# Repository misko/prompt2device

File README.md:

# prompt2device

The separate [vNext PCB skill and orchestrator](vnext/README.md) package is
available alongside the reference workflow below; existing projects keep their
accepted toolchain until an explicit migration.

The [Crow carrier + pod public design package](projects/crow-array/README.md)
provides native designs and fabrication exports for the 5-carrier/10-pod prototype
batch. It is a subset of the local sealed release, **not order authorization**.

**Prompt to device:** give an agent a plain-language hardware brief, work
through explicit design, review, and physical-test cycles, and finish with the
artifacts needed to manufacture the device—not merely a plausible CAD image.

## Quick start

### 1. Give the PCB skill a brief

```text
/pcb-design 3S LiPo input → 4× USB-A outputs at 5 V / 1.5 A each + 1× USB-C output at 5 V / 5 A.
```

### 2. See fabricated examples

These two projects show the path from a plain-English request to electrical
CAD, mechanical CAD, and fabricated hardware. The prompt cells preserve the
compact original wording; the links retain the corresponding design-lineage
records. Photographs are bench evidence, not production-qualification claims.
Exact provenance and claim limits are in
[`fabricated-examples.md`](docs/fabricated-examples.md).

|  | **Pluto eight-way fast switch** | **3S LiPo USB power board** |
|---|---|---|
| **Prompt** | [“we want a high speed 8 antenna switching board that can be programmed by the rpi4 and run with a pluto+”](archived_projects/pluto-rx2-8way/01_docs/BRIEF.md#original-prompt) | [“Please from scratch start a new project, and lets design a board that takes 3S lipo XT60 power as input , and outputs 3 x USB A ports (2.5A max) and 1 x USB C port (6A max).”](archived_projects/usb-power-3s/01_docs/BRIEF.md#original-prompt) |
| **PCB rendering** |  |  |
| **Enclosure rendering** |  |  |
| **Fabricated board** |  |  |
| **Board in enclosure** |  |  |
| **Bench setup** |  |  |

[`pluto-rx2-8way-v5`](projects/pluto-rx2-8way-v5/) is the fabricated
eight-way RF switch board. Its immutable PCB design archive is
[`v0.2.1-2026-08-14`](projects/pluto-rx2-8way-v5/07_releases/v0.2.1-2026-08-14/),
with a sealed
[3D PCB render](projects/pluto-rx2-8way-v5/07_releases/v0.2.1-2026-08-14/verification/final_iso_3200.png),
and its independently versioned
[`v0.8.0-2026-08-28` enclosure](projects/pluto-rx2-8way-v5/07_enclosure_releases/v0.8.0-2026-08-28/)
has a corresponding
[installed-assembly render](projects/pluto-rx2-8way-v5/07_enclosure_releases/v0.8.0-2026-08-28/renders/installed-assembly.png).
That enclosure remains an honest `INCOMPLETE` candidate pending sliced and
printed fit, retention, connector-service, and thermal tests.
The PCB archive itself predates fabrication and still records
`DO-NOT-ORDER`; RF first-article measurements remain open.
The current human-readable engineering study is
[RF isolation, leakage paths, and a v6 mitigation strategy](projects/pluto-rx2-8way-v5/01_docs/reports/2026-08-27-rf-isolation-and-v6-mitigation.md).

[`usb-hub-3s-v3`](projects/usb-hub-3s-v3/) is the closest existing hardware
to the quick-start brief: three USB-A outputs and one USB-C output rather than
four USB-A outputs. Its latest sealed and fabricated archive is
[`v1.12-2026-07-28`](projects/usb-hub-3s-v3/07_releases/v1.12-2026-07-28/).
The [bring-up journal](projects/usb-hub-3s-v3/01_docs/journal/bringup.md)
records physical v1.12 boards and the replacement assembly's successful
no-load regulation checks; full load, transient, and thermal qualification is
still open.

The exact v1.12 board also has an independently versioned
[`v0.4.0-2026-08-28` enclosure](projects/usb-hub-3s-v3/07_enclosure_releases/v0.4.0-2026-08-28/)
with a corresponding
[installed-assembly render](projects/usb-hub-3s-v3/07_enclosure_releases/v0.4.0-2026-08-28/renders/installed-assembly.png).
Its [authored source and replay instructions](projects/usb-hub-3s-v3/03_src/mechanical/README.md)
remain mutable, while the release is an immutable `INCOMPLETE` candidate:
structural and collision screens pass, but printed fit, connector service,
retention, and thermal evidence remain open.

### 3. Follow the prompt-to-device loop

```text
plain-language brief
  → fact locks and architecture
  → schematic, placement, routing, and enclosure development
  ↺ independent review, correction, regeneration, and measurement
  → sealed fabrication and mechanical artifacts
  → first article, physical findings, and the next development cycle
```

Today the governed output can include:

- native KiCad schematics and a rendered schematic PDF;
- the routed KiCad PCB plus Gerbers, drill files, BOM, and CPL for fabrication;
- top, bottom, and 3D PCB renders plus a STEP assembly;
- when mechanical work is selected, enclosure source, printable STLs, assembly
  renders, and clearance evidence; and
- governed Markdown investigations under each project's `01_docs/reports/`.

The pipeline already uses board-level CAD/assembly twins as verification
instruments. Governed firmware releases and an integrated product-level digital
twin are forward work, tracked by
[IMP-234](improvements.md#imp-234--firmware-release-stream) and
[IMP-236](improvements.md#imp-236--prompt-to-device-product-composition-and-digital-twin).

## What this repository is

`prompt2device` is a code-first prompt-to-device engineering system. It turns a
user brief into generated KiCad source, bounded routing candidates,
independently graded fabrication evidence, immutable releases, printable
enclosures, and measured first-article records.

The product is the workflow under [`skills/`](skills/). Boards under
[`projects/`](projects/) are its active applications; sealed release folders
are immutable evidence, not templates to copy.

## Manual commissioning

Clone the repository, create a branch, and save the user's original request as
a UTF-8 text file:

```bash
git clone https://github.com/misko/prompt2device.git
cd prompt2device
git switch -c codex/my-board
```

Create the governed project scaffold and choose its capability profile:

```bash
python3 skills/pcb-design/scripts/commission_project.py my-board \
  --brief-file /path/to/original-brief.txt \
  --signal-integrity ordinary \
  --assembly jlcpcb \
  --firmware forbidden \
  --target design
```

Use `high_speed_digital` for USB and similar controlled digital links. Use
`rf` only when the board intentionally carries RF/microwave signals. Add
`--foreign-mating` when the floorplan consumes geometry from third-party
hardware. Run the command with `--help` for enclosure and target options.
Here `--assembly jlcpcb` selects the populated JLCPCB PCBA evidence path, not
merely bare-board fabrication.

The command reports `PCB-SCAFFOLD OK` and leaves `PCB-COMMISSION` explicitly
`INCOMPLETE`. It preserves the prompt and creates an executable commission
hold; it does not accept requirements, adopt the seeded schema examples, or
run a board producer.

Inspect the selected lifecycle before spending engineering time:

```bash
python3 skills/pcb-design/scripts/skill_reference_router.py \
  --profile projects/my-board/01_docs/capability-profile.json \
  --at-stage PCB-COMMISSION \
  --json
```

Then give Codex this instruction:

```text
Read and follow skills/pcb-design/SKILL.md for projects/my-board. Preserve the
original brief, close the commission fact locks, and stop at the first evidence
or operator checkpoint. Do not create firmware unless the brief explicitly
asks.
```

Do not run `rebuild_all.sh` yet. The scaffold contains visible schema examples
and `01_docs/COMMISSIONING-HOLD.md`; both rebuild conductors refuse to run until
the commission boundary is reviewed and that marker is deliberately removed.

Start with [`skills/pcb-design/SKILL.md`](skills/pcb-design/SKILL.md). Its
canonical lifecycle and runnable command map is
[`execution-graph.md`](skills/pcb-design/references/execution-graph.md).

## How execution is structured

The repository deliberately separates three layers:

```text
capability profile
  -> disclosure graph (what stages/references are selected)
  -> project conductor (what bounded commands actually run)
  -> owning gates (what exact subjects passed)
  -> review/seal/publication/physical claims
```

- The router is planning only. Its output is never execution evidence.
- `projects/<name>/03_src/rebuild_all.sh` is the full source/schematic
  conductor. It intentionally pauses at review and operator checkpoints.
- `rebuild_reuse.sh` is the deterministic route-authority replay when the
  schematic is unchanged; `route.yaml` selects the authenticated source.
- Fresh route exploration is a separate candidate workflow; canonical rebuild
  replays the authenticated route source selected by `route.yaml`.
- Layout seal, PCB release seal, publication, ordering, and first article are
  different claims with different owners.

The declarative lifecycle is:

```text
commission -> architecture -> sourcing
  -> schematic -> placement -> routing -> layout seal
  -> fabrication -> assembly verification
  -> release review -> release seal
  -> publication | first article -> production
```

RF context/source/realized/fabrication stages and foreign-mating import are
conditional branches. High-speed digital composes inside the ordinary stages.
Enclosures have an implemented parallel **INCOMPLETE-candidate** release stream
and may bind an unchanged PCB release without resealing it. Higher readiness
still requires the enclosure skill's recomputable CAD and physical evidence.
Firmware is currently an explicit handoff,
not a governed release stream; [IMP-234](improvements.md#imp-234--firmware-release-stream)
tracks that missing boundary.

## Skills and authority

| Skill | Owns |
|---|---|
| [`pcb-design`](skills/pcb-design/SKILL.md) | Commission, lifecycle composition, backtracking, reviews, release seal, publication, first article. |
| [`kicad-pcb`](skills/kicad-pcb/SKILL.md) | TSX/KiCad schematic conversion, netlist/parity, placement, geometry, routing, DRC, SI/RF realization. |
| [`jlcpcb-fab`](skills/jlcpcb-fab/SKILL.md) | Gerber/drill/BOM/CPL, stock/population/rotation, JLC CAD twin, manufacturer staging, bring-up cards. |
| [`pcb-enclosure`](skills/pcb-enclosure/SKILL.md) | Mechanical commission, PCB interface binding, independent fasteners, motion/clearance, mesh/physical evidence, enclosure releases. |
| [`shopping-list`](skills/shopping-list/SKILL.md) | Provenance-bound purchase lists for self-supplied parts. |

Authority is singular. A skill links to another owner's procedure rather than
copying it. Project `contracts.md` files own exact artifact membership. Script
`--help` text owns exact flags. [`improvements.md`](improvements.md) tracks
work and rationale but never overrides an executable gate or accepted ADR.

## Repository map

| Path | Purpose |
|---|---|
| [`skills/`](skills/) | Reusable workflow, references, tools, and project templates. |
| [`projects/`](projects/) | Active boards, including manufactured and still-evolving designs. |
| [`archived_projects/`](archived_projects/) | Retired scaffolds and frozen regression/history units. |
| [`docs/`](docs/) | Documentation index, accepted ADRs, measured proof, and historical context. |
| [`tests/`](tests/) | Clean and known-bad fixtures proving gates can both pass and fail. |
| [`external_hardware/`](external_hardware/) | Measured/cited facts about foreign devices this repo must mate with. |
| [`improvements.md`](improvements.md) | Forward work registry and retained improvement history. |

See [`docs/README.md`](docs/README.md) for the documentation authority map.

## Design model

The board is generated from committed human-owned source:

- TSX/tscircuit is the standard schematic authoring front end.
- Shared scripts convert the circuit, generate KiCad geometry/rules, and grade
  exact identities. Per-board source is configuration, not a copied backend.
- KiCad's Python API owns geometry and saves; `kicad-cli` owns headless
  ERC/DRC/netlist/export checks.
- Routing operates on immutable candidates. Only a clean, independently graded
  candidate can become the promoted route chain.
- Generated `04_kicad/` is a mutable current snapshot and is never hand-source
  authority. Immutable history lives under release streams.

This makes design changes diffable and rebuildable. It also means a generator
defect can become a physical defect, so freshness, parity, nonzero coverage,
registered models, and independent review are first-class gates.

## Claims and releases

A release is an immutable reviewed candidate archive. It is not automatically
an order event. A design can be electrically sound and sealed while remaining
`DO-NOT-ORDER` because stock, uploader selections, physical fit, or first-
article evidence is owed.

PCB and enclosure versions are independent streams. Current enclosure release
tooling publishes immutable `INCOMPLETE` candidates bound to one exact PCB
release without forcing that PCB to be resealed; it does not yet publish a
higher readiness claim from caller-supplied scope status.
A future firmware stream, exact product lock, and integrated product-level
digital twin remain tracked work, not current release authority.

## Toolchain

Core documentation and planning use normal Python 3. KiCad operations require
the KiCad-bundled Python where `import pcbnew` succeeds plus `kicad-cli`.
TSX generation requires the pinned tscircuit/Bun environment. Fresh routing
requires the configured KiCadRoutingTools installation; replaying a selected
authenticated route authority does not.

Python entry points expose `--help`; shell-conductor forms are documented in
the execution graph. Use the owning current command rather than copying an old
invocation from a project journal.

## Validate a workflow change

At minimum:

```bash
python3 skills/pcb-design/scripts/skill_authority_check.py
python3 tests/t1_skill_progressive_disclosure.py
python3 tests/t1_pcb_documentation.py
python3 scripts/contracts_audit.py --walk --root skills/pcb-design
```

Run the domain suites affected by the change, then commit at a green boundary.

## License

Except where otherwise noted, all original content in this repository is
licensed under the [MIT License](LICENSE). This includes software,
documentation, prompts, schematics, PCB layouts, mechanical CAD files,
and generated design artifacts.

Third-party materials remain subject to their respective copyright and
license terms and are not relicensed by this repository.

See [third-party notices](THIRD_PARTY_NOTICES.md) for material provenance and
[contribution guidelines](CONTRIBUTING.md) for new submissions.

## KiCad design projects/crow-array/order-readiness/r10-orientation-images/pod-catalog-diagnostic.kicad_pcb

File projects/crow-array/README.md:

# Crow carrier and microphone pod

[Open the public v3 design package](releases/crow-prototype-v3-first-run-5c10p-public-v1/README.md).
It contains **5 carrier / 10 pod** design quantities, native KiCad files, PDFs,
Gerbers, BOM/CPL, population policy and retained verification records.

This is a redistribution-reviewed subset, not the full original sealed offline
replay. The original design verdict is SOUND; the ordering verdict remains
**DO-NOT-ORDER**. No firmware or manufactured-hardware qualification is supplied.
The package index exposes all nine exact-job holds and its excluded dependencies.

For the current assembly split, sourcing worksheets and browser-based ordering
continuation, start with the [MacBook handoff](order-readiness/MACBOOK-HANDOFF.md).
These mutable preparation records do not change the immutable release verdict.

`publication.py verify` checks the actual file census, trusted source hashes,
both board roles, local native libraries, license/handoff policy and Gerber ZIPs.
`test_publication.py` corrupts isolated copies to prove that the checker refuses
missing boards, altered/rehashed payloads, added assets and misleading claims.
This verification is separate from the repository's legacy release-format gate.

Validation on 2026-10-25: 15 public-package regression tests passed; independent
[publication review](checks/publication-review-20261025.json) passed. The
[isolated native replot check](checks/native-20261025.json) regenerated all 26
Gerber/drill members and all eight PDFs with matching geometry/rendered pages.
Both boards passed strict DRC, connectivity and explicit schematic parity with
zero findings; refilling zones did not change native geometry. The check used
only this public package and vNext tools, not the original sealed archive.
This does not replay the excluded mechanical/runtime/engineering evidence.

To repeat the native check on the supported KiCad 10.0.4/Poppler host:

```sh
/usr/bin/python3 -B projects/crow-array/native_smoke.py --output /absolute/absent-result.json
```

Portable CI verifies the package and its negative controls, not this native run.

The exporter refuses an existing destination. Rebuild in an absent temporary
directory using explicit paths to the original sealed repository and its parent
project (for post-seal evidence):

```sh
python3 -B projects/crow-array/publication.py build \
  --sealed /absolute/path/to/original-sealed-repository \
  --post-seal-project /absolute/path/to/original-project \
  --package /absolute/path/to/absent-public-candidate
```

The trusted `publication-policy.json` freezes this derivative's generated notices,
external-dependency inventory and handoff. Changes require explicit review of
that policy and a separately identified package; never rewrite the original seal.

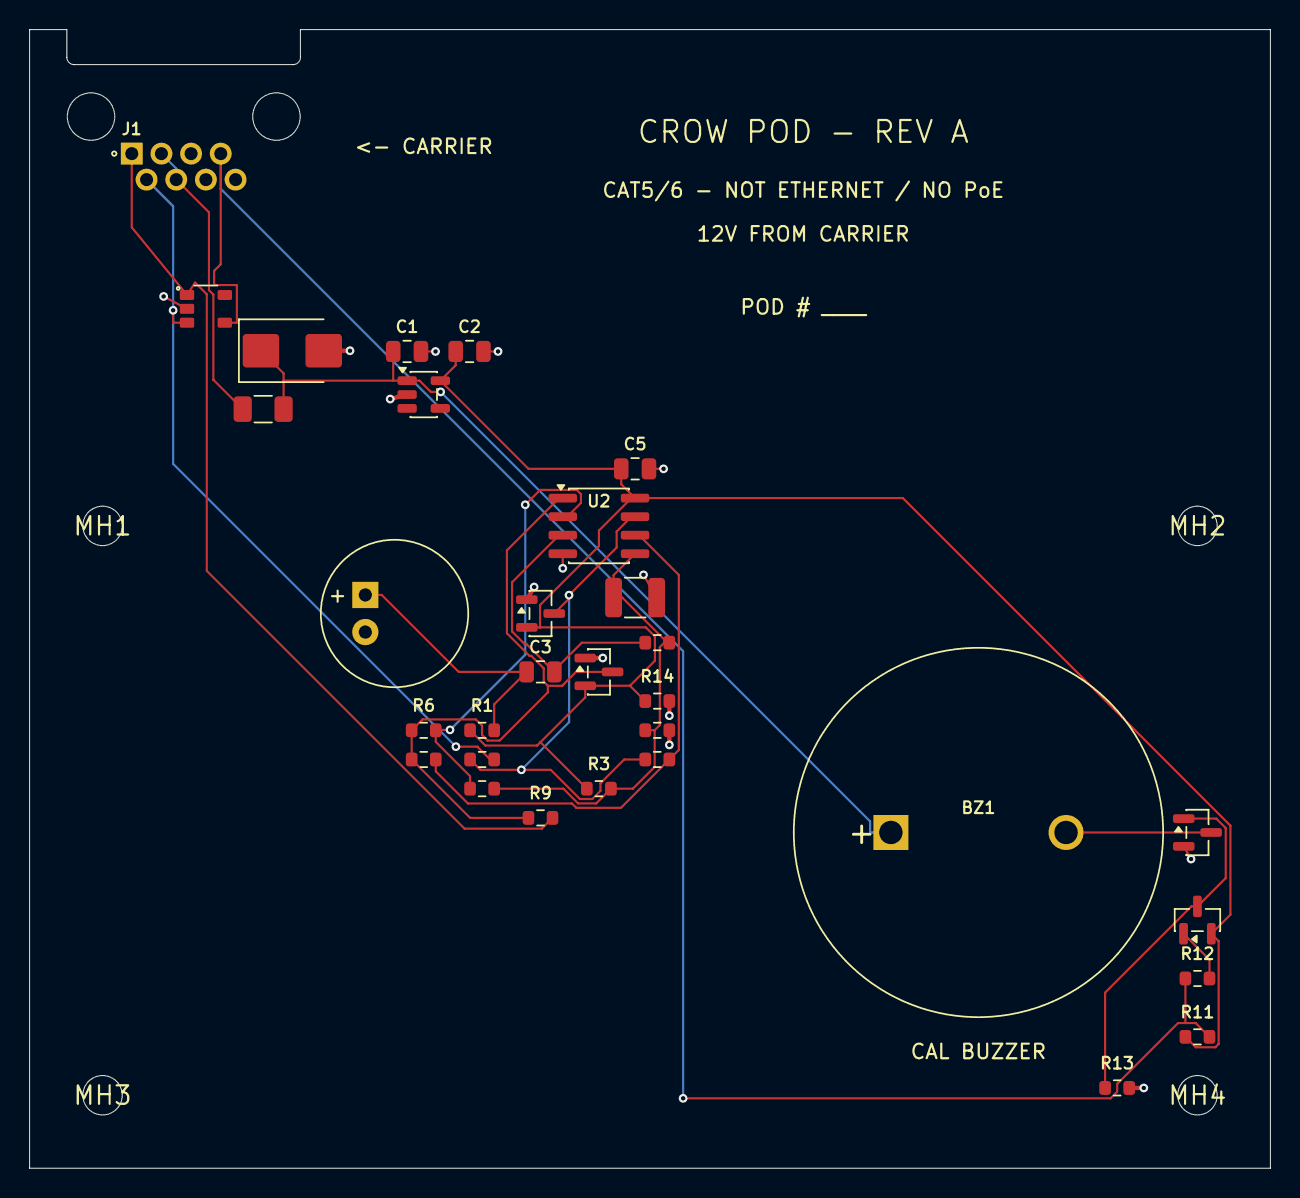
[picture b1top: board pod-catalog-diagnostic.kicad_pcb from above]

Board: 4 copper layers, 85.0 x 78.0 mm, 35 parts (0 on the bottom side), 17 nets.

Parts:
BZ1: CPE-203
C1: 2.2uF 50V X7R 10%; C_0805_2012Metric
C2: 10uF 10V X7R 20%; C_0805_2012Metric
C3: 1uF 50V X7R 10%; C_0805_2012Metric
C4: 47uF 10V X7R 20%; C_1210_3225Metric
C5: 100nF 10V X7R; C_0805_2012Metric
D1: Littelfuse SMBJ15A; D_SMB
D2, D3: BAT54S-7-F; SOT-23
D4: SP0504BAHTG
F1: 1206L010/30NR; Fuse_1206_3216Metric
J1: RJHSE-5080
MH1, MH2, MH3, MH4: NPTH mounting
MIC1: CMA-4544PF-W electret capsule; CMA-4544PF-W
Q1: DMN3023L-7; SOT-23
Q2: MMBT3906LT1G; SOT-23
R1: 2.2k 1%; R_0603_1608Metric
R2, R13: 100k 1%; R_0603_1608Metric
R3, R4, R7, R8, R11, R12: 10k 1%; R_0603_1608Metric
R5: 1k 1%; R_0603_1608Metric
R6: 39k 1%; R_0603_1608Metric
R9, R10: 1k 1% 0.125W; R_0603_1608Metric
R14: 330R 1% 0.125W; R_0603_1608Metric
U1: TPS70933DBVR; SOT-23-5
U2: TLV9062IDR; SOIC-8_3.9x4.9mm_P1.27mm

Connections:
/3V3: C2.1, C5.1, D2.2, D3.2, Q2.2, R1.1, R3.1, R11.1, R14.1, U1.5, U2.8
/12V: BZ1.1, C1.1, D1.1, F1.2, U1.1
/12V_RAW: F1.1, J1.3, J1.4
/AMP_M: D3.3, R8.1, R10.1, U2.7
/AMP_P: D2.3, R6.1, R7.1, R9.1, U2.1
/AUDIO_M: D4.3, J1.2, R10.2
/AUDIO_P: D4.1, J1.1, R9.2
/BUZZ_N: D4.4, J1.7, R11.2, R12.1
/BZ_BASE: Q2.1, R12.2
/BZ_GATE: Q1.1, Q2.3, R13.1
/BZ_LOW: BZ1.2, Q1.3
/GND: C1.2, C2.2, C4.2, C5.2, D1.2, D2.1, D3.1, D4.2, J1.5, J1.6, J1.8, MIC1.2, Q1.2, R4.2, R13.2, R14.2, U1.2, U2.4
/INV_A: R5.1, R6.2, U2.2
/INV_B: R7.2, R8.2, U2.6
/MIC_AC: C3.2, R2.1, U2.3
/MIC_NODE: C3.1, MIC1.1, R1.2
/VMID: C4.1, R2.2, R3.2, R4.1, R5.2, U2.5

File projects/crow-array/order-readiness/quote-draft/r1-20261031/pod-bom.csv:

Comment,Designator,Footprint,JLCPCB Part #,Manufacturer,MPN,Quantity,Assembly route,Supply route
100k 1%,"R13,R2",Resistor_SMD:R_0603_1608Metric,C844916,Vishay,CRCW0603100KFKEA,2,JLC_SMT_requested,JLC_catalog
100nF 10V X7R,C5,Capacitor_SMD:C_0805_2012Metric,C1711,Samsung Electro-Mechanics,CL21B104KBCNNNC,1,JLC_SMT_requested,JLC_catalog
10k 1%,"R11,R12,R3,R4,R7,R8",Resistor_SMD:R_0603_1608Metric,C844918,Vishay,CRCW060310K0FKEA,6,JLC_SMT_requested,JLC_catalog
10uF 10V X7R 20%,C2,Capacitor_SMD:C_0805_2012Metric,C710992,Murata,GRM21BR71A106MA73L,1,JLC_SMT_requested,JLC_catalog
1206L010/30WR,F1,Fuse:Fuse_1206_3216Metric,C2153988,Littelfuse,1206L010/30WR,1,JLC_SMT_requested,JLC_regular_replenishment
1k 1%,R5,Resistor_SMD:R_0603_1608Metric,C844747,Vishay,CRCW06031K00FKEAHP,1,JLC_SMT_requested,JLC_catalog
1k 1% 0.125W,"R10,R9",Resistor_SMD:R_0603_1608Metric,C844747,Vishay,CRCW06031K00FKEAHP,2,JLC_SMT_requested,JLC_catalog
1uF 10V X7R,C3,Capacitor_SMD:C_0805_2012Metric,C97917,Murata,GRM21BR71A105KA01L,1,JLC_SMT_requested,JLC_regular_replenishment
2.2k 1%,R1,Resistor_SMD:R_0603_1608Metric,C844925,Vishay,CRCW06032K20FKEA,1,JLC_SMT_requested,JLC_catalog
2.2uF 35V X7R 20%,C1,Capacitor_SMD:C_0805_2012Metric,C2167593,TDK,C2012X7R1V225K125AE,1,JLC_SMT_requested,JLC_regular_replenishment
330R 1% 0.125W,R14,Resistor_SMD:R_0603_1608Metric,C844355,Vishay,CRCW0603330RFKEAHP,1,JLC_SMT_requested,JLC_catalog
39k 1%,R6,Resistor_SMD:R_0603_1608Metric,C844779,Vishay,CRCW060339K0FKEA,1,JLC_SMT_requested,JLC_catalog
47uF 10V X7R 20%,C4,Capacitor_SMD:C_1210_3225Metric,C84494,Murata,GRM32ER71A476KE15L,1,JLC_SMT_requested,JLC_catalog
BAT54S-7-F,"D2,D3",Package_TO_SOT_SMD:SOT-23,C83574,Diodes Incorporated,BAT54S-7-F,2,JLC_SMT_requested,JLC_catalog
DMN3023L-7,Q1,Package_TO_SOT_SMD:SOT-23,C443825,Diodes Incorporated,DMN3023L-7,1,JLC_SMT_requested,JLC_catalog
Littelfuse SMBJ15A,D1,Diode_SMD:D_SMB,C83846,Littelfuse,SMBJ15A,1,JLC_SMT_requested,JLC_catalog
MMBT3906LT1G,Q2,Package_TO_SOT_SMD:SOT-23,C53444,onsemi,MMBT3906LT1G,1,JLC_SMT_requested,JLC_catalog
RJHSE-5080,J1,CrowPhysical:RJHSE-5080,C599441,Amphenol,RJHSE-5080,1,JLC_manual_requested,JLC_catalog
SP0504BAHTG,D4,CrowPhysical:SP0504BAHTG,C10675,Littelfuse,SP0504BAHTG,1,JLC_SMT_requested,JLC_catalog
TLV9062IDR,U2,Package_SO:SOIC-8_3.9x4.9mm_P1.27mm,C398355,Texas Instruments,TLV9062IDR,1,JLC_SMT_requested,JLC_catalog
TPS70933DBVR,U1,Package_TO_SOT_SMD:SOT-23-5,C89347,Texas Instruments,TPS70933DBVR,1,JLC_SMT_requested,JLC_catalog

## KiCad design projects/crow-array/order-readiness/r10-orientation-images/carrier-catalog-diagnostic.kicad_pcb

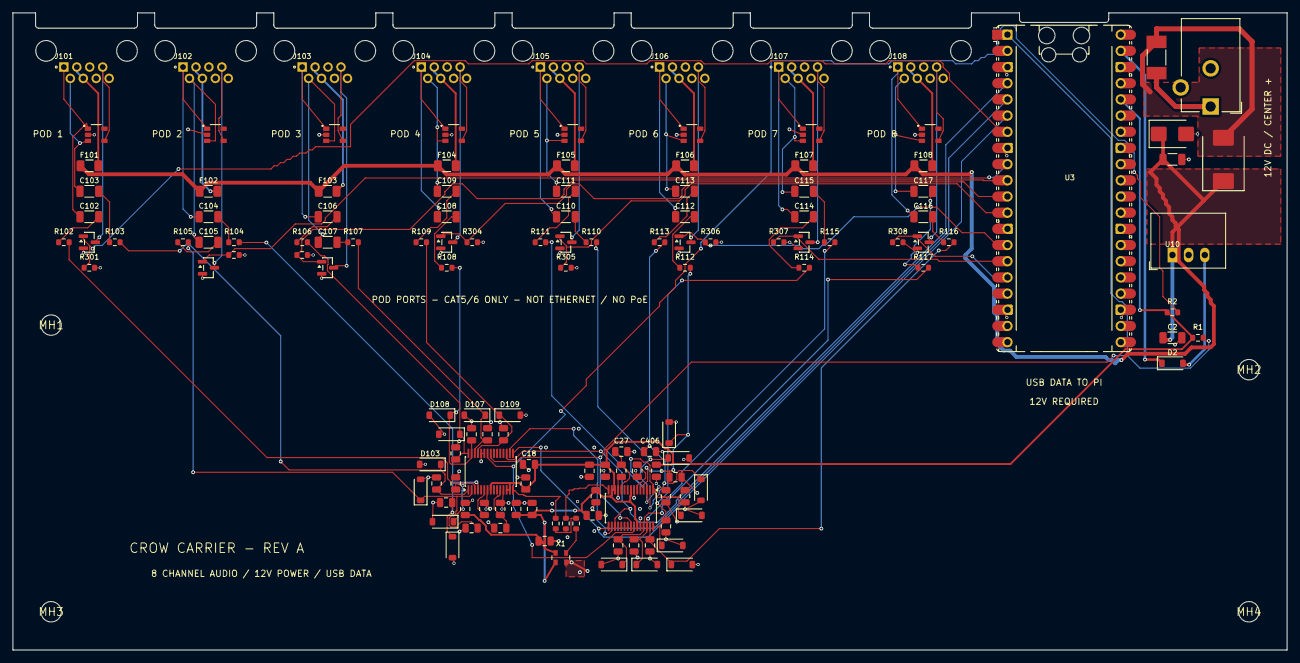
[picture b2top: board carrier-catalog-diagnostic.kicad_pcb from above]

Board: 4 copper layers, 200.0 x 100.0 mm, 142 parts (0 on the bottom side), 92 nets.

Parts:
C1, C2: 10uF 50V X7R 10%; C_1206_3216Metric
C4: 1uF 50V X7R 10% CLOCK; C_0805_2012Metric
C11, C21: 1uF 50V X7R 10% VREF; C_0805_2012Metric
C12, C22: 100nF 10V X7R LDO; C_0805_2012Metric
C13, C23: 100nF 10V X7R AVDD; C_0805_2012Metric
C14, C24: 10uF 10V X7R AVDD; C_0805_2012Metric
C15, C25: 100nF 10V X7R DVDD; C_0805_2012Metric
C16, C26: 10uF 10V X7R DVDD; C_0805_2012Metric
C17, C27: 10uF 10V X7R LDO; C_0805_2012Metric
C18, C28: 100nF 10V X7R IOVDD; C_0805_2012Metric
C102, C103, C104, C105, C106, C107, C108, C109, C110, C111, C112, C113, C114, C115, C116, C117: 2.2uF 25V X7R 20%; C_1206_3216Metric
C301, C302, C303, C304, C305, C306, C307, C308, C401, C402, C403, C404, C405, C406, C407, C408: 2.2nF 50V C0G 5%; C_0805_2012Metric
D1: Littelfuse SMBJ15A; D_SMB
D2: Diodes Inc 1N5819HW-7-F; D_SOD-123
D3: SS34-E3/57T; D_SMC
D102, D103, D104, D105, D106, D107, D108, D109, D110, D111, D112, D113, D114, D115, D116, D117: BZT52C3V9-7-F; D_SOD-123
D501, D502, D503, D504, D505, D506, D507, D508: SP0504BAHTG
F1: 0451001.MRL 1A; Fuse_Littelfuse-NANO2-451_453
F101, F102, F103, F104, F105, F106, F107, F108: 1206L010/30NR; Fuse_1206_3216Metric
J1: PJ-102AH / 12V CENTER POSITIVE; BarrelJack_CUI_PJ-102AH_Horizontal
J101, J102, J103, J104, J105, J106, J107, J108: RJHSE-5080
MH1, MH2, MH3, MH4: NPTH mounting
Q101, Q102, Q103, Q104, Q105, Q106, Q107, Q108: DMN3023L-7; SOT-23
R1, R2: 4.7k 1%; R_0603_1608Metric
R3: 68R 1% 0.1W 25V; R_0603_1608Metric
R4, R5: 56R 1% 0.1W 25V; R_0603_1608Metric
R102, R103, R104, R105, R106, R107, R108, R109, R110, R111, R112, R113, R114, R115, R116, R117: 2.7k 1%; R_0603_1608Metric
R301, R302, R303, R304, R305, R306, R307, R308: 100k 1%; R_0603_1608Metric
U1, U2: PCM1864DBTR; TSSOP-30_4.4x7.8mm_P0.5mm
U3: Pico SC0915 MOD: on-module D1 DEPOPULATED; RaspberryPi_Pico_Common_Unspecified
U10: TSR 1-2450; Converter_DCDC_TRACO_TSR1_RetainedLands
X1: LMK6CE012288CDLFR; TI_LMK6C_DLF0004A

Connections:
/3V3: C4.1, C13.1, C14.1, C15.1, C16.1, C18.1, C23.1, C24.1, C25.1, C26.1, C28.1, R1.1, R2.1, U1.8, U1.13, U1.14, U2.8, U2.13, U2.14, U2.25, U3.36, X1.1, X1.4
/5V: D2.2, U10.3
/12V: C1.1, C2.1, D1.1, D3.1, F101.1, F102.1, F103.1, F104.1, F105.1, F106.1, F107.1, F108.1, U10.1
/ADC1_CH1_M: C401.1, D103.1, R103.2, U1.1
/ADC1_CH1_P: C301.1, D102.1, R102.2, U1.3
/ADC1_CH2_M: C402.1, D105.1, R105.2, U1.2
/ADC1_CH2_P: C302.1, D104.1, R104.2, U1.4
/ADC1_CH3_M: C403.1, D107.1, R107.2, U1.28
/ADC1_CH3_P: C303.1, D106.1, R106.2, U1.30
/ADC1_CH4_M: C404.1, D109.1, R109.2, U1.27
/ADC1_CH4_P: C304.1, D108.1, R108.2, U1.29
/ADC2_CH1_M: C405.1, D111.1, R111.2, U2.1
/ADC2_CH1_P: C305.1, D110.1, R110.2, U2.3
/ADC2_CH2_M: C406.1, D113.1, R113.2, U2.2
/ADC2_CH2_P: C306.1, D112.1, R112.2, U2.4
/ADC2_CH3_M: C407.1, D115.1, R115.2, U2.28
/ADC2_CH3_P: C307.1, D114.1, R114.2, U2.30
/ADC2_CH4_M: C408.1, D117.1, R117.2, U2.27
/ADC2_CH4_P: C308.1, D116.1, R116.2, U2.29
/BCK: U1.17, U2.17, U3.5
/BUZZ_GPIO1: Q101.1, R301.1, U3.7
/BUZZ_GPIO2: Q102.1, R302.1, U3.9
/BUZZ_GPIO3: Q103.1, R303.1, U3.10
/BUZZ_GPIO4: Q104.1, R304.1, U3.11
/BUZZ_GPIO5: Q105.1, R305.1, U3.12
/BUZZ_GPIO6: Q106.1, R306.1, U3.14
/BUZZ_GPIO7: Q107.1, R307.1, U3.15
/BUZZ_GPIO8: Q108.1, R308.1, U3.16
/FUSED12: D3.2, F1.2
/GND: C1.2, C2.2, C4.2, C11.2, C12.2, C13.2, C14.2, C15.2, C16.2, C17.2, C18.2, C21.2, C22.2, C23.2, C24.2, C25.2, C26.2, C27.2, C28.2, C301.2, C302.2, C303.2, C304.2, C305.2, C306.2, C307.2, C308.2, C401.2, C402.2, C403.2, C404.2, C405.2, C406.2, C407.2, C408.2, D1.2, D102.2, D103.2, D104.2, D105.2, D106.2, D107.2, D108.2, D109.2, D110.2, D111.2, D112.2, D113.2, D114.2, D115.2, D116.2, D117.2, D501.2, D502.2, D503.2, D504.2, D505.2, D506.2, D507.2, D508.2, J1.2, J101.5, J101.6, J101.8, J102.5, J102.6, J102.8, J103.5, J103.6, J103.8, J104.5, J104.6, J104.8, J105.5, J105.6, J105.8, J106.5, J106.6, J106.8, J107.5, J107.6, J107.8, J108.5, J108.6, J108.8, Q101.2, Q102.2, Q103.2, Q104.2, Q105.2, Q106.2, Q107.2, Q108.2, R301.2, R302.2, R303.2, R304.2, R305.2, R306.2, R307.2, R308.2, U1.7, U1.12, U1.25, U1.26, U2.7, U2.12, U2.26, U3.3, U3.8, U3.13, U3.18, U3.23, U3.28, U3.33, U3.38, U10.2, X1.2
/LDO1: C12.1, C17.1, U1.11
/LDO2: C22.1, C27.1, U2.11
/LRCK: U1.16, U2.16, U3.6
/MCLK_ADC1: R4.2, U1.15
/MCLK_ADC2: R5.2, U2.15
/MCLK_FAN: R3.2, R4.1, R5.1
/MCLK_SRC: R3.1, X1.3
/P1_12V: F101.2, J101.3, J101.4
/P1_A_M: C103.1, D501.3, J101.2
/P1_A_P: C102.1, D501.1, J101.1
/P1_BUZZ_N: D501.4, J101.7, Q101.3
/P1_CM: C103.2, R103.1
/P1_CP: C102.2, R102.1
/P2_12V: F102.2, J102.3, J102.4
/P2_A_M: C105.1, D502.3, J102.2
/P2_A_P: C104.1, D502.1, J102.1
/P2_BUZZ_N: D502.4, J102.7, Q102.3
/P2_CM: C105.2, R105.1
/P2_CP: C104.2, R104.1
/P3_12V: F103.2, J103.3, J103.4
/P3_A_M: C107.1, D503.3, J103.2
/P3_A_P: C106.1, D503.1, J103.1
/P3_BUZZ_N: D503.4, J103.7, Q103.3
/P3_CM: C107.2, R107.1
/P3_CP: C106.2, R106.1
/P4_12V: F104.2, J104.3, J104.4
/P4_A_M: C109.1, D504.3, J104.2
/P4_A_P: C108.1, D504.1, J104.1
/P4_BUZZ_N: D504.4, J104.7, Q104.3
/P4_CM: C109.2, R109.1
/P4_CP: C108.2, R108.1
/P5_12V: F105.2, J105.3, J105.4
/P5_A_M: C111.1, D505.3, J105.2
/P5_A_P: C110.1, D505.1, J105.1
/P5_BUZZ_N: D505.4, J105.7, Q105.3
/P5_CM: C111.2, R111.1
/P5_CP: C110.2, R110.1
/P6_12V: F106.2, J106.3, J106.4
/P6_A_M: C113.1, D506.3, J106.2
/P6_A_P: C112.1, D506.1, J106.1
/P6_BUZZ_N: D506.4, J106.7, Q106.3
/P6_CM: C113.2, R113.1
/P6_CP: C112.2, R112.1
/P7_12V: F107.2, J107.3, J107.4
/P7_A_M: C115.1, D507.3, J107.2
/P7_A_P: C114.1, D507.1, J107.1
/P7_BUZZ_N: D507.4, J107.7, Q107.3
/P7_CM: C115.2, R115.1
/P7_CP: C114.2, R114.1
/P8_12V: F108.2, J108.3, J108.4
/P8_A_M: C117.1, D508.3, J108.2
/P8_A_P: C116.1, D508.1, J108.1
/P8_BUZZ_N: D508.4, J108.7, Q108.3
/P8_CM: C117.2, R117.1
/P8_CP: C116.2, R116.1
/REF1: C11.1, U1.6
/REF2: C21.1, U2.6
/SCL: R2.2, U1.24, U2.24, U3.2
/SDA: R1.2, U1.23, U2.23, U3.1
/TDM: U1.18, U2.18, U3.4
/VIN12: F1.1, J1.1
/VSYS: D2.1, U3.39

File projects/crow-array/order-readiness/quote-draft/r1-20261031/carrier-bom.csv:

Comment,Designator,Footprint,JLCPCB Part #,Manufacturer,MPN,Quantity,Assembly route,Supply route
0451001.MRL 1A,F1,Fuse:Fuse_Littelfuse-NANO2-451_453,C3099,Littelfuse,0451001.MRL,1,JLC_SMT_requested,JLC_catalog
100k 1%,"R301,R302,R303,R304,R305,R306,R307,R308",Resistor_SMD:R_0603_1608Metric,C844916,Vishay,CRCW0603100KFKEA,8,JLC_SMT_requested,JLC_catalog
100nF 10V X7R,C4,Capacitor_SMD:C_0805_2012Metric,C1711,Samsung Electro-Mechanics,CL21B104KBCNNNC,1,JLC_SMT_requested,JLC_catalog
100nF 10V X7R AVDD,"C13,C23",Capacitor_SMD:C_0805_2012Metric,C1711,Samsung Electro-Mechanics,CL21B104KBCNNNC,2,JLC_SMT_requested,JLC_catalog
100nF 10V X7R DVDD,"C15,C25",Capacitor_SMD:C_0805_2012Metric,C1711,Samsung Electro-Mechanics,CL21B104KBCNNNC,2,JLC_SMT_requested,JLC_catalog
100nF 10V X7R IOVDD,"C18,C28",Capacitor_SMD:C_0805_2012Metric,C1711,Samsung Electro-Mechanics,CL21B104KBCNNNC,2,JLC_SMT_requested,JLC_catalog
100nF 10V X7R LDO,"C12,C22",Capacitor_SMD:C_0805_2012Metric,C1711,Samsung Electro-Mechanics,CL21B104KBCNNNC,2,JLC_SMT_requested,JLC_catalog
10uF 10V X7R AVDD,"C14,C24",Capacitor_SMD:C_0805_2012Metric,C710992,Murata,GRM21BR71A106MA73L,2,JLC_SMT_requested,JLC_catalog
10uF 10V X7R DVDD,"C16,C26",Capacitor_SMD:C_0805_2012Metric,C710992,Murata,GRM21BR71A106MA73L,2,JLC_SMT_requested,JLC_catalog
10uF 10V X7R LDO,"C17,C27",Capacitor_SMD:C_0805_2012Metric,C710992,Murata,GRM21BR71A106MA73L,2,JLC_SMT_requested,JLC_catalog
10uF 35V X7R 20%,"C1,C2",Capacitor_SMD:C_1206_3216Metric,C2182140,TDK,C3216X7R1V106K160AC,2,JLC_SMT_requested,JLC_regular_replenishment
1206L010/30WR,"F101,F102,F103,F104,F105,F106,F107,F108",Fuse:Fuse_1206_3216Metric,C2153988,Littelfuse,1206L010/30WR,8,JLC_SMT_requested,JLC_regular_replenishment
1uF 10V X7R VREF,"C11,C21",Capacitor_SMD:C_0805_2012Metric,C97917,Murata,GRM21BR71A105KA01L,2,JLC_SMT_requested,JLC_regular_replenishment
2.2nF 50V C0G 5%,"C301,C302,C303,C304,C305,C306,C307,C308,C401,C402,C403,C404,C405,C406,C407,C408",Capacitor_SMD:C_0805_2012Metric,C28260,Samsung Electro-Mechanics,CL21C222JBFNNNE,16,JLC_SMT_requested,JLC_catalog
2.2uF 25V X7R 20%,"C102,C103,C104,C105,C106,C107,C108,C109,C110,C111,C112,C113,C114,C115,C116,C117",Capacitor_SMD:C_1206_3216Metric,C97962,Murata,GRM31MR71E225KA93L,16,JLC_SMT_requested,JLC_catalog
2.7k 1%,"R102,R103,R104,R105,R106,R107,R108,R109,R110,R111,R112,R113,R114,R115,R116,R117",Resistor_SMD:R_0603_1608Metric,C844770,Vishay,CRCW06032K70FKEA,16,JLC_SMT_requested,JLC_catalog
4.7k 1%,"R1,R2",Resistor_SMD:R_0603_1608Metric,C844931,Vishay,CRCW06034K70FKEA,2,JLC_SMT_requested,JLC_catalog
56R 1% 0.1W 25V,"R4,R5",Resistor_SMD:R_0603_1608Metric,C844179,Vishay Dale,CRCW060356R0FKEA,2,JLC_SMT_requested,JLC_catalog
68R 1% 0.1W 25V,R3,Resistor_SMD:R_0603_1608Metric,C403329,Panasonic Industry,ERJ-3EKF68R0V,1,JLC_SMT_requested,JLC_catalog
BZT52C3V9-7-F,"D102,D103,D104,D105,D106,D107,D108,D109,D110,D111,D112,D113,D114,D115,D116,D117",Diode_SMD:D_SOD-123,C154917,Diodes Incorporated,BZT52C3V9-7-F,16,JLC_SMT_requested,JLC_catalog
CB3LV-3I-12M288000,X1,CrowPhysical:CTS_CB3LV_7050,C17275161,CTS-Frequency Controls,CB3LV-3I-12M288000,1,JLC_SMT_requested,JLC_regular_replenishment
DMN3023L-7,"Q101,Q102,Q103,Q104,Q105,Q106,Q107,Q108",Package_TO_SOT_SMD:SOT-23,C443825,Diodes Incorporated,DMN3023L-7,8,JLC_SMT_requested,JLC_catalog
Diodes Inc 1N5819HW-7-F,D2,Diode_SMD:D_SOD-123,C82544,Diodes Incorporated,1N5819HW-7-F,1,JLC_SMT_requested,JLC_catalog
Littelfuse SMBJ15A,D1,Diode_SMD:D_SMB,C83846,Littelfuse,SMBJ15A,1,JLC_SMT_requested,JLC_catalog
PCM1864DBT,"U1,U2",Package_SO:TSSOP-30_4.4x7.8mm_P0.5mm,,Texas Instruments,PCM1864DBT,2,JLC_SMT_requested,JLC_Global_Sourcing
PJ-102AH / 12V CENTER POSITIVE,J1,Connector_BarrelJack:BarrelJack_CUI_PJ-102AH_Horizontal,C3096093,Same Sky,PJ-102AH,1,JLC_manual_requested,JLC_catalog
R-78E5.0-0.5,U10,Converter_DCDC:Converter_DCDC_RECOM_R-78E-0.5_THT,,RECOM Power,R-78E5.0-0.5,1,JLC_manual_requested,JLC_Global_Sourcing
RJHSE-5080,"J101,J102,J103,J104,J105,J106,J107,J108",CrowPhysical:RJHSE-5080,C599441,Amphenol,RJHSE-5080,8,JLC_manual_requested,JLC_catalog
SP0504BAHTG,"D501,D502,D503,D504,D505,D506,D507,D508",CrowPhysical:SP0504BAHTG,C10675,Littelfuse,SP0504BAHTG,8,JLC_SMT_requested,JLC_catalog
SS34-E3/57T,D3,Diode_SMD:D_SMC,C13354,Vishay,SS34-E3/57T,1,JLC_SMT_requested,JLC_catalog
